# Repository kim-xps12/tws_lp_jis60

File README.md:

# tws_lp_jis60

## About

JIS配列・ロープロファイル・完全無線の左右分割60%キーボードです。

## Concept

[sphh jp v2 (a bit keys)](https://abitkeys.com/sphhjp/build_v2.html) のHHKB-likeなJIS配列を分割化したコンセプトを継承し、完全無線化とロープロファイル化を加えた設計です。

- JIS 60%配列（ISOエンター、矢印キー付き）
- 完全無線（PC接続も左右間もBLE）
- Kailh Choc v2 互換ホットスワップ
- PCBサンドイッチ構造
- ZMK Firmware によるキーマップ変更
- XIAO nRF52840 搭載

設計の詳細は設計者の note 記事を参照してください: [JIS配列でロープロファイルな完全無線の左右分割キーボードを作った話](https://note.com/b_sky_lab/n/n9fbacc2c5264)

## How to Build

ビルドガイドは Web 版（[https://b-sky-lab.github.io/tws_lp_jis60/](https://b-sky-lab.github.io/tws_lp_jis60/)）を参照してください。ソースは [docs/build_guide/build_guide.md](docs/build_guide/build_guide.md) です。

ファームウェア（ZMKシールドモジュール）は [b-sky-lab/tws_lp_shield_module](https://github.com/b-sky-lab/tws_lp_shield_module) で管理されています。

## Where to Get

<!-- TODO: Booth頒布開始後にリンクを追加 -->
準備中

## License

このリポジトリは CC-BY-SA-4.0（Creative Commons Attribution-ShareAlike 4.0 International）でライセンスされています．

詳細は [LICENSE](./LICENSE) を参照してください.

### Third-Party Components

本プロジェクトは，以下の第三者ライブラリのコンポーネントを利用しています：

#### 1. OPL_Kicad_Library (CC-BY-SA-4.0)
- fork元: https://github.com/Seeed-Studio/OPL_Kicad_Library
- fork先: https://github.com/kim-xps12/OPL_Kicad_Library
- ライセンス: CC-BY-SA-4.0
- 変更ファイル: `XIAO-nRF52840-DIP.kicad_mod`（DRCシルク警告の修正）
- 利用箇所: [pcb_data/kicad_library/external/OPL_Kicad_Library](pcb_data/kicad_library/external/OPL_Kicad_Library)（submodule）

#### 2. KiCAD_FootPrint (MIT)
- fork元: https://github.com/Salicylic-acid3/KiCAD_FootPrint
- fork先: https://github.com/kim-xps12/KiCAD_FootPrint
- ライセンス: MIT
- 変更ファイル: `Diode_TH_SMD.kicad_mod`（DRCシルク警告の修正）
- 利用箇所: [pcb_data/kicad_library/external/KiCAD_FootPrint](pcb_data/kicad_library/external/KiCAD_FootPrint)（submodule）

#### 3. MX_V2 (MIT)
- fork元: https://github.com/ai03-2725/MX_V2
- 利用ディレクトリ:[custom-library.pretty](pcb_data/kicad_library/custom-library.pretty)
- ライセンス: MIT
- 派生物: `pcb_data/kicad_library/custom-library.pretty/`内のカスタムフットプリント
- 帰属表示: 当該ディレクトリ内の[LICENSE_MX_V2.txt](pcb_data/kicad_library/custom-library.pretty/LICENSE_MX_V2.txt)を参照

### Why CC-BY-SA-4.0？

本作のライセンスがCC-BY-SA-4.0である理由は，PCB設計ファイルにOPL_Kicad_Libraryから改変したフットプリントを組み込んでいるからです．CC-BY-SA-4.0のShareAlike条項により，派生物も同じCC-BY-SA-4.0ライセンスを継承する必要があります．

MITライセンスのコンポーネント（KiCAD_FootPrint，MX_V2）は，適切な帰属表示を維持することでCC-BY-SA-4.0と互換性があります．

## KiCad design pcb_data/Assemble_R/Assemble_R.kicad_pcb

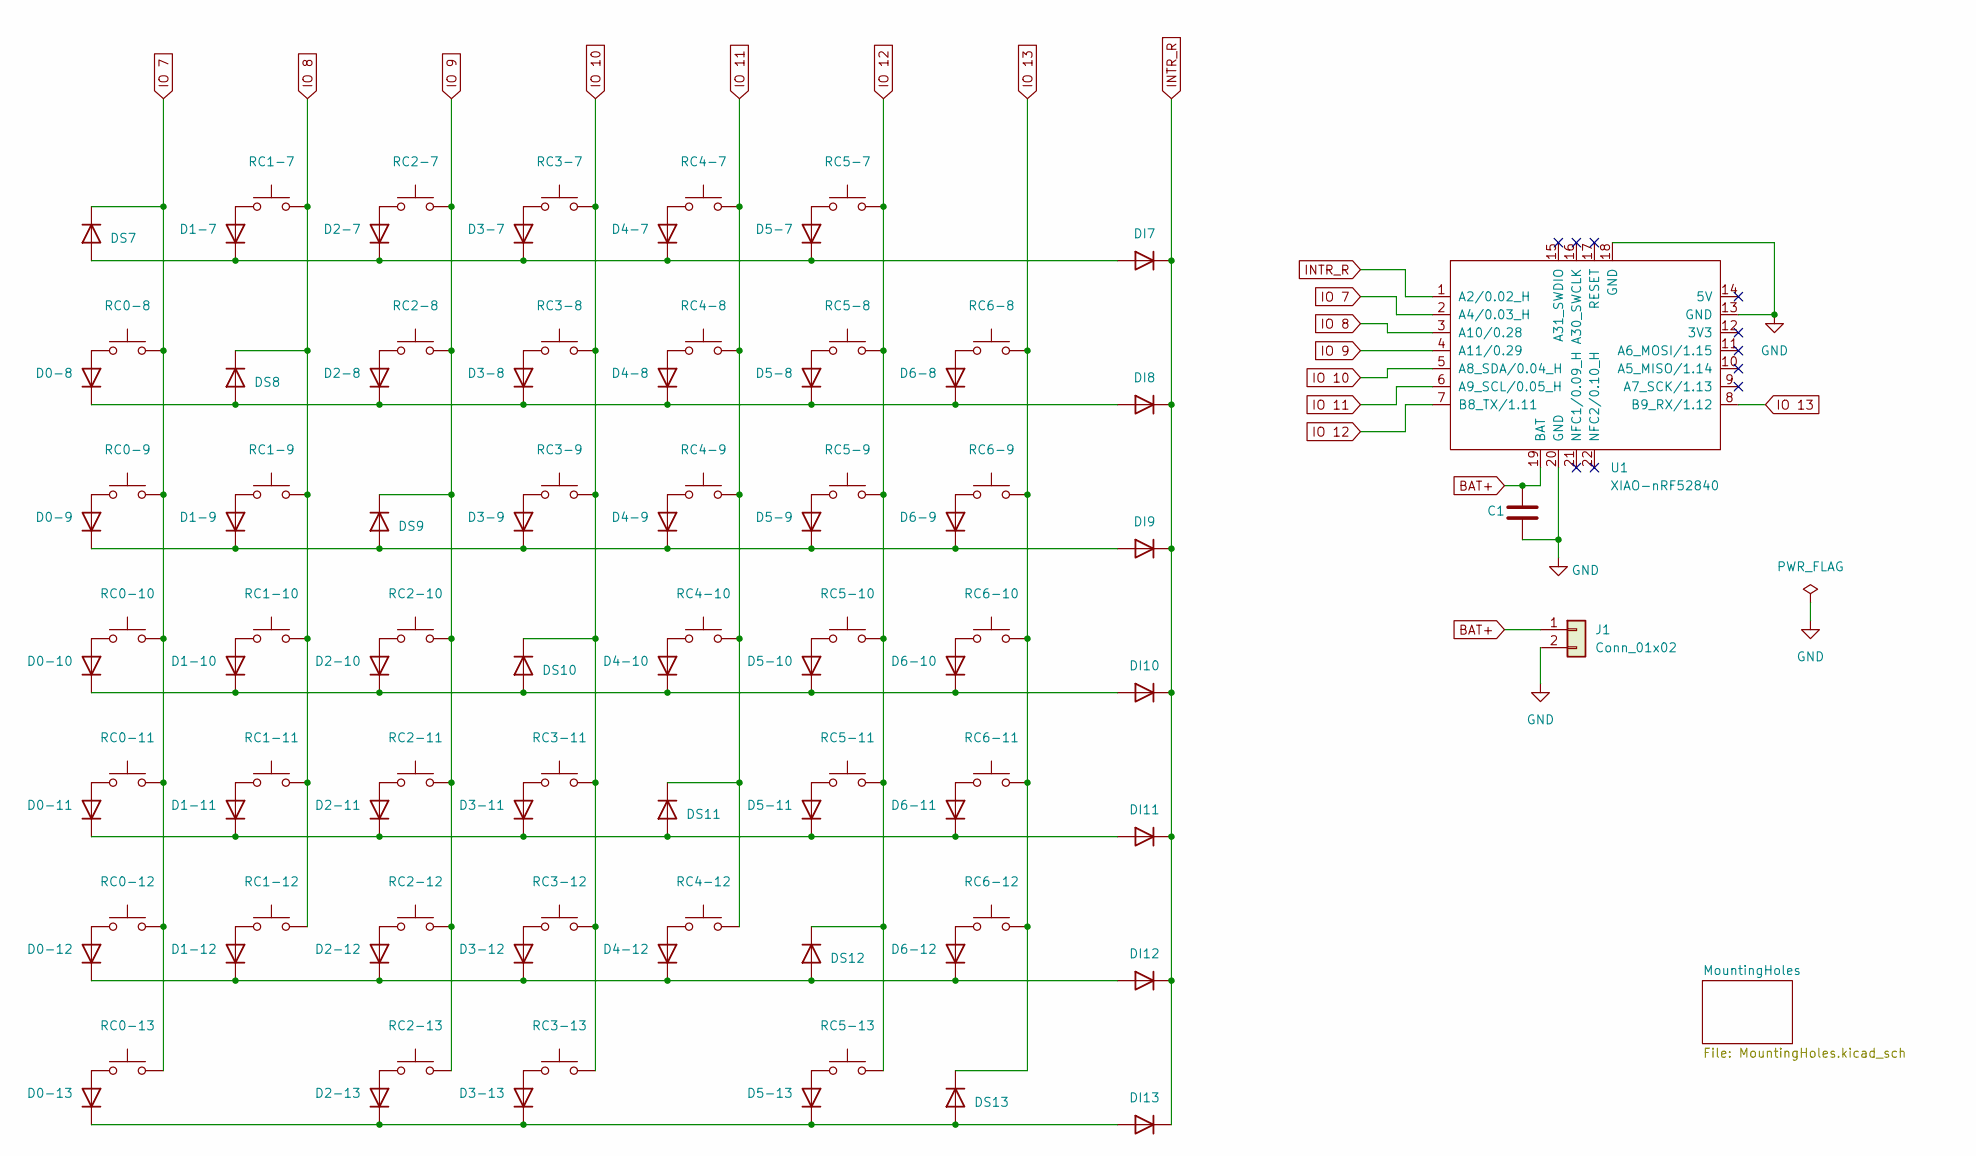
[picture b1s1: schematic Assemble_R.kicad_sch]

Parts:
C1: GRM32EC81C476KE15L; C_1210_3225Metric_Pad1.33x2.70mm_HandSolder
D0-8, D0-9, D0-10, D0-11, D0-12, D0-13, D1-7, D1-9, D1-10, D1-11, D1-12, D2-7, D2-8, D2-10, D2-11, D2-12, D2-13, D3-7, D3-8, D3-9, D3-11, D3-12, D3-13, D4-7, D4-8, D4-9, D4-10, D4-12, D5-7, D5-8, D5-9, D5-10, D5-11, D5-13, D6-8, D6-9, D6-10, D6-11, D6-12: 1N4148W; Diode_TH_SMD
DI7, DI8, DI9, DI10, DI11, DI12, DI13: 1N4148W; Diode_TH_SMD
DS7, DS8, DS9, DS10, DS11, DS12, DS13: 1N4148W; Diode_TH_SMD
J1: Conn_01x02; JST_PH_B2B-PH-K_1x02_P2.00mm_Vertical
RC0-8, RC0-9, RC0-10, RC0-11, RC0-12, RC1-7, RC1-9, RC1-10, RC1-11, RC1-12, RC2-7, RC2-8, RC2-10, RC2-11, RC2-12, RC2-13, RC3-7, RC3-8, RC3-9, RC3-11, RC3-12, RC3-13, RC4-7, RC4-8, RC4-9, RC4-10, RC4-12, RC5-7, RC5-8, RC5-9, RC5-10, RC5-11, RC5-13, RC6-8, RC6-9, RC6-11, RC6-12: SW_Push; Kailh-PG1353-Hotswap-R-1U
RC0-13: SW_Push; Kailh-PG1353-Hotswap-R-1.25U
RC6-10: SW_Push; Kailh-PG1353-Hotswap-ISOEnter-R
U1: XIAO-nRF52840; xiao-ble-smd-cutout

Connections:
BAT+: C1.1, J1.1, U1.19 (BAT)
GND: C1.2, J1.2, U1.13 (GND), U1.18 (GND), U1.20 (GND)
INTR_R: DI7.1 (K), DI8.1 (K), DI9.1 (K), DI10.1 (K), DI11.1 (K), DI12.1 (K), DI13.1 (K), U1.1 (A2/0.02_H)
IO 7: DS7.1 (K), RC0-8.1, RC0-9.1, RC0-10.1, RC0-11.1, RC0-12.1, RC0-13.1, U1.2 (A4/0.03_H)
IO 8: DS8.1 (K), RC1-7.1, RC1-9.1, RC1-10.1, RC1-11.1, RC1-12.1, U1.3 (A10/0.28)
IO 9: DS9.1 (K), RC2-7.1, RC2-8.1, RC2-10.1, RC2-11.1, RC2-12.1, RC2-13.1, U1.4 (A11/0.29)
IO 10: DS10.1 (K), RC3-7.1, RC3-8.1, RC3-9.1, RC3-11.1, RC3-12.1, RC3-13.1, U1.5 (A8_SDA/0.04_H)
IO 11: DS11.1 (K), RC4-7.1, RC4-8.1, RC4-9.1, RC4-10.1, RC4-12.1, U1.6 (A9_SCL/0.05_H)
IO 12: DS12.1 (K), RC5-7.1, RC5-8.1, RC5-9.1, RC5-10.1, RC5-11.1, RC5-13.1, U1.7 (B8_TX/1.11)
IO 13: DS13.1 (K), RC6-8.1, RC6-9.1, RC6-10.1, RC6-11.1, RC6-12.1, U1.8 (B9_RX/1.12)
unnamed: D0-8.2 (A), RC0-8.2
unnamed: D0-8.1 (K), D2-8.1 (K), D3-8.1 (K), D4-8.1 (K), D5-8.1 (K), D6-8.1 (K), DI8.2 (A), DS8.2 (A)
unnamed: D0-9.2 (A), RC0-9.2
unnamed: D0-9.1 (K), D1-9.1 (K), D3-9.1 (K), D4-9.1 (K), D5-9.1 (K), D6-9.1 (K), DI9.2 (A), DS9.2 (A)
unnamed: D0-10.2 (A), RC0-10.2
unnamed: D0-10.1 (K), D1-10.1 (K), D2-10.1 (K), D4-10.1 (K), D5-10.1 (K), D6-10.1 (K), DI10.2 (A), DS10.2 (A)
unnamed: D0-11.2 (A), RC0-11.2
unnamed: D0-11.1 (K), D1-11.1 (K), D2-11.1 (K), D3-11.1 (K), D5-11.1 (K), D6-11.1 (K), DI11.2 (A), DS11.2 (A)
unnamed: D0-12.2 (A), RC0-12.2
unnamed: D0-12.1 (K), D1-12.1 (K), D2-12.1 (K), D3-12.1 (K), D4-12.1 (K), D6-12.1 (K), DI12.2 (A), DS12.2 (A)
unnamed: D0-13.2 (A), RC0-13.2
unnamed: D0-13.1 (K), D2-13.1 (K), D3-13.1 (K), D5-13.1 (K), DI13.2 (A), DS13.2 (A)
unnamed: D1-7.2 (A), RC1-7.2
unnamed: D1-7.1 (K), D2-7.1 (K), D3-7.1 (K), D4-7.1 (K), D5-7.1 (K), DI7.2 (A), DS7.2 (A)
unnamed: D1-9.2 (A), RC1-9.2
unnamed: D1-10.2 (A), RC1-10.2
unnamed: D1-11.2 (A), RC1-11.2
unnamed: D1-12.2 (A), RC1-12.2
unnamed: D2-7.2 (A), RC2-7.2
unnamed: D2-8.2 (A), RC2-8.2
unnamed: D2-10.2 (A), RC2-10.2
unnamed: D2-11.2 (A), RC2-11.2
unnamed: D2-12.2 (A), RC2-12.2
unnamed: D2-13.2 (A), RC2-13.2
unnamed: D3-7.2 (A), RC3-7.2
unnamed: D3-8.2 (A), RC3-8.2
unnamed: D3-9.2 (A), RC3-9.2
unnamed: D3-11.2 (A), RC3-11.2
unnamed: D3-12.2 (A), RC3-12.2
unnamed: D3-13.2 (A), RC3-13.2
unnamed: D4-7.2 (A), RC4-7.2
unnamed: D4-8.2 (A), RC4-8.2
unnamed: D4-9.2 (A), RC4-9.2
unnamed: D4-10.2 (A), RC4-10.2
unnamed: D4-12.2 (A), RC4-12.2
unnamed: D5-7.2 (A), RC5-7.2
unnamed: D5-8.2 (A), RC5-8.2
unnamed: D5-9.2 (A), RC5-9.2
unnamed: D5-10.2 (A), RC5-10.2
unnamed: D5-11.2 (A), RC5-11.2
unnamed: D5-13.2 (A), RC5-13.2
unnamed: D6-8.2 (A), RC6-8.2
unnamed: D6-9.2 (A), RC6-9.2
unnamed: D6-10.2 (A), RC6-10.2
unnamed: D6-11.2 (A), RC6-11.2
unnamed: D6-12.2 (A), RC6-12.2

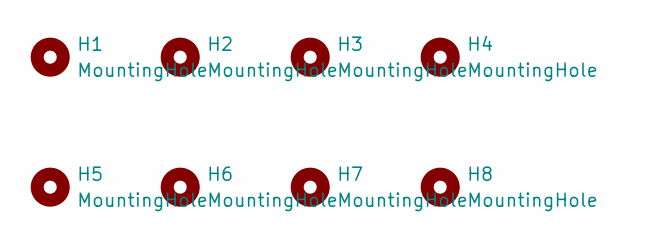
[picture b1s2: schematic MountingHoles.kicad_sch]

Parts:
H1, H2, H3, H4, H5, H6, H7, H8: MountingHole; m2_Spacer_Hole

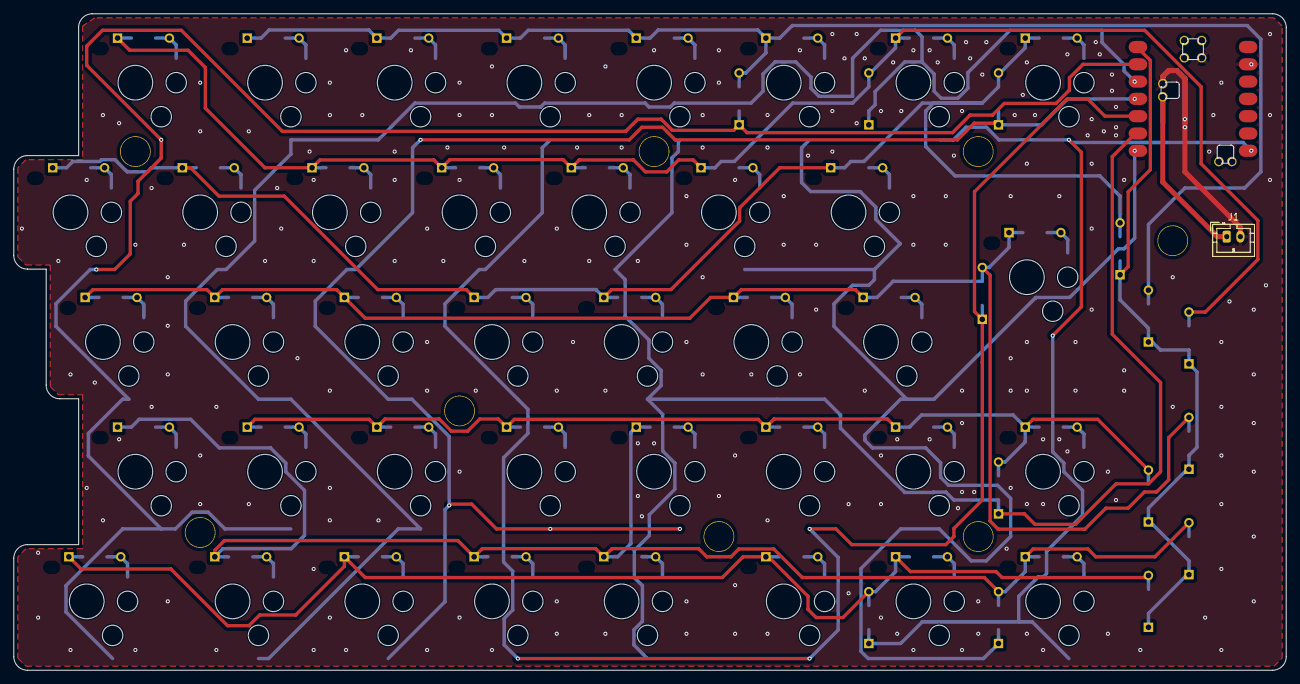
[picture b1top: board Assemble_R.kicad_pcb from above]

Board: 2 copper layers, 186.9 x 96.4 mm, 103 parts (1 on the bottom side), 56 nets.

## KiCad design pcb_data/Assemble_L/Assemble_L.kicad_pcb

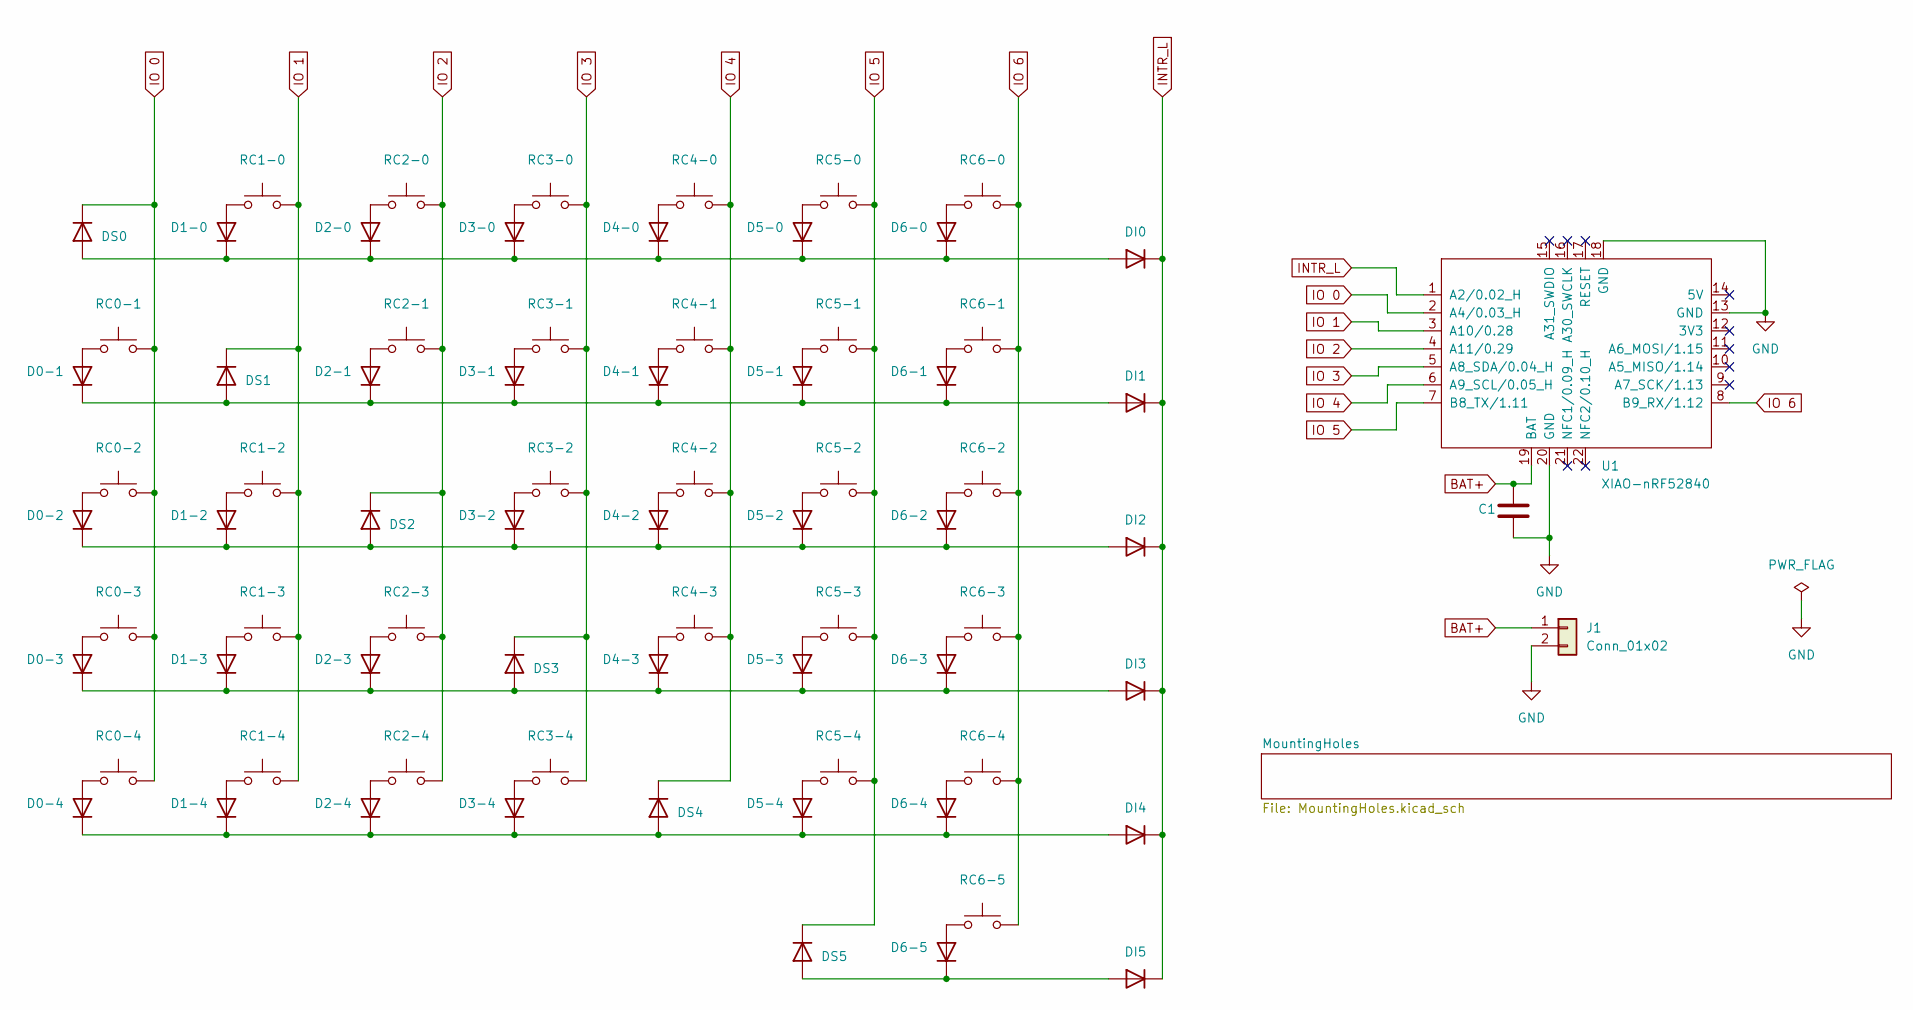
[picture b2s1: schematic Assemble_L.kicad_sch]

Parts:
C1: GRM32EC81C476KE15L; C_1210_3225Metric_Pad1.33x2.70mm_HandSolder
D0-1, D0-2, D0-3, D0-4, D1-0, D1-2, D1-3, D1-4, D2-0, D2-1, D2-3, D2-4, D3-0, D3-1, D3-2, D3-4, D4-0, D4-1, D4-2, D4-3, D5-0, D5-1, D5-2, D5-3, D5-4, D6-0, D6-1, D6-2, D6-3, D6-4, D6-5: 1N4148W; Diode_TH_SMD
DI0, DI1, DI2, DI3, DI4, DI5: 1N4148W; Diode_TH_SMD
DS0, DS1, DS2, DS3, DS4, DS5: 1N4148W; Diode_TH_SMD
J1: Conn_01x02; JST_PH_B2B-PH-K_1x02_P2.00mm_Vertical
RC0-1: SW_Push; Kailh-PG1353-Hotswap-L-1.5U
RC0-2: SW_Push; Kailh-PG1353-Hotswap-L-1.75U
RC0-3: SW_Push; Kailh-PG1353-Hotswap-L-2U
RC0-4, RC1-0, RC1-2, RC1-3, RC1-4, RC2-0, RC2-1, RC2-3, RC2-4, RC3-0, RC3-1, RC3-2, RC3-4, RC4-0, RC4-1, RC4-2, RC4-3, RC5-0, RC5-1, RC5-2, RC5-3, RC5-4, RC6-0, RC6-1, RC6-2, RC6-3, RC6-4: SW_Push; Kailh-PG1353-Hotswap-L-1U
RC6-5: SW_Push; Kailh-PG1353-Hotswap-L-1.25U
U1: XIAO-nRF52840; xiao-ble-smd-cutout

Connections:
BAT+: C1.1, J1.1, U1.19 (BAT)
GND: C1.2, J1.2, U1.13 (GND), U1.18 (GND), U1.20 (GND)
INTR_L: DI0.1 (K), DI1.1 (K), DI2.1 (K), DI3.1 (K), DI4.1 (K), DI5.1 (K), U1.1 (A2/0.02_H)
IO 0: DS0.1 (K), RC0-1.1, RC0-2.1, RC0-3.1, RC0-4.1, U1.2 (A4/0.03_H)
IO 1: DS1.1 (K), RC1-0.1, RC1-2.1, RC1-3.1, RC1-4.1, U1.3 (A10/0.28)
IO 2: DS2.1 (K), RC2-0.1, RC2-1.1, RC2-3.1, RC2-4.1, U1.4 (A11/0.29)
IO 3: DS3.1 (K), RC3-0.1, RC3-1.1, RC3-2.1, RC3-4.1, U1.5 (A8_SDA/0.04_H)
IO 4: DS4.1 (K), RC4-0.1, RC4-1.1, RC4-2.1, RC4-3.1, U1.6 (A9_SCL/0.05_H)
IO 5: DS5.1 (K), RC5-0.1, RC5-1.1, RC5-2.1, RC5-3.1, RC5-4.1, U1.7 (B8_TX/1.11)
IO 6: RC6-0.1, RC6-1.1, RC6-2.1, RC6-3.1, RC6-4.1, RC6-5.1, U1.8 (B9_RX/1.12)
unnamed: D0-1.2 (A), RC0-1.2
unnamed: D0-1.1 (K), D2-1.1 (K), D3-1.1 (K), D4-1.1 (K), D5-1.1 (K), D6-1.1 (K), DI1.2 (A), DS1.2 (A)
unnamed: D0-2.2 (A), RC0-2.2
unnamed: D0-2.1 (K), D1-2.1 (K), D3-2.1 (K), D4-2.1 (K), D5-2.1 (K), D6-2.1 (K), DI2.2 (A), DS2.2 (A)
unnamed: D0-3.2 (A), RC0-3.2
unnamed: D0-3.1 (K), D1-3.1 (K), D2-3.1 (K), D4-3.1 (K), D5-3.1 (K), D6-3.1 (K), DI3.2 (A), DS3.2 (A)
unnamed: D0-4.2 (A), RC0-4.2
unnamed: D0-4.1 (K), D1-4.1 (K), D2-4.1 (K), D3-4.1 (K), D5-4.1 (K), D6-4.1 (K), DI4.2 (A), DS4.2 (A)
unnamed: D1-0.2 (A), RC1-0.2
unnamed: D1-0.1 (K), D2-0.1 (K), D3-0.1 (K), D4-0.1 (K), D5-0.1 (K), D6-0.1 (K), DI0.2 (A), DS0.2 (A)
unnamed: D1-2.2 (A), RC1-2.2
unnamed: D1-3.2 (A), RC1-3.2
unnamed: D1-4.2 (A), RC1-4.2
unnamed: D2-0.2 (A), RC2-0.2
unnamed: D2-1.2 (A), RC2-1.2
unnamed: D2-3.2 (A), RC2-3.2
unnamed: D2-4.2 (A), RC2-4.2
unnamed: D3-0.2 (A), RC3-0.2
unnamed: D3-1.2 (A), RC3-1.2
unnamed: D3-2.2 (A), RC3-2.2
unnamed: D3-4.2 (A), RC3-4.2
unnamed: D4-0.2 (A), RC4-0.2
unnamed: D4-1.2 (A), RC4-1.2
unnamed: D4-2.2 (A), RC4-2.2
unnamed: D4-3.2 (A), RC4-3.2
unnamed: D5-0.2 (A), RC5-0.2
unnamed: D5-1.2 (A), RC5-1.2
unnamed: D5-2.2 (A), RC5-2.2
unnamed: D5-3.2 (A), RC5-3.2
unnamed: D5-4.2 (A), RC5-4.2
unnamed: D6-0.2 (A), RC6-0.2
unnamed: D6-1.2 (A), RC6-1.2
unnamed: D6-2.2 (A), RC6-2.2
unnamed: D6-3.2 (A), RC6-3.2
unnamed: D6-4.2 (A), RC6-4.2
unnamed: D6-5.2 (A), RC6-5.2
unnamed: D6-5.1 (K), DI5.2 (A), DS5.2 (A)

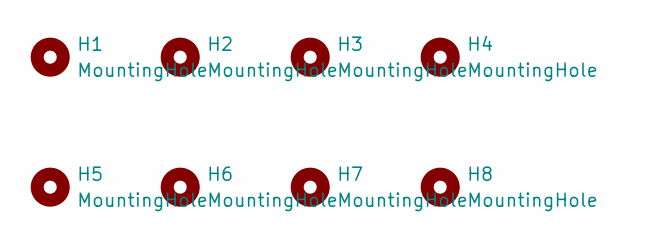
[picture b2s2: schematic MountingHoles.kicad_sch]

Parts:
H1, H2, H3, H4, H5, H6, H7, H8: MountingHole; m2_Spacer_Hole

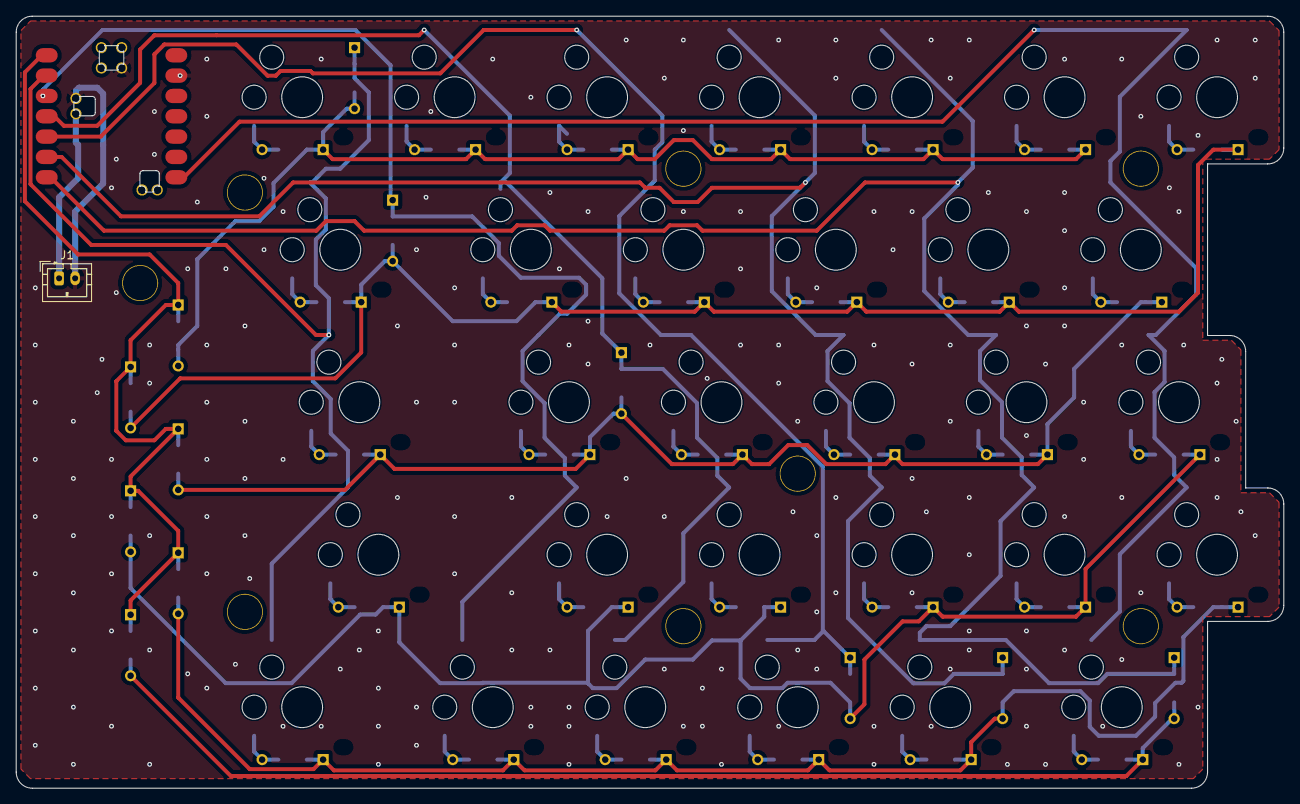
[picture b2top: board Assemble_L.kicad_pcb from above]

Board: 2 copper layers, 158.4 x 96.4 mm, 85 parts (1 on the bottom side), 47 nets.

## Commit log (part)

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2025-12-03 add .gitignore
2025-12-03 Add submodule: OPL_Kicad_Library
2025-12-03 Add submodule: MX_V2
2025-12-03 Add submodule: KiCAD_FootPrint
2025-12-03 add keyboard layout file
2025-12-03 add custom fp
2025-12-03 add kicad file
2025-12-06 complete to design pattern of board L
2025-12-06 Update submodules: resolve DRC warning about silk
2025-12-06 Update submodule URLs to kim-xps12 forks
2025-12-07 fix line width 0.2 -> 0.5
2025-12-07 add GND plane
2025-12-07 complete to design pattern of board R
2025-12-07 add README and LICENCE of custom footprint
2025-12-07 update foot print reference, and fix GND filling area DRC error
2025-12-07 add 3d model
2025-12-07 add licence details
2025-12-17 add licence details (#3)
    マージして閉じます
2025-12-17 Feat/add kicad pro (#4)
    * add .gitignore
    * Add submodule: OPL_Kicad_Library
    * Add submodule: MX_V2
    * Add submodule: KiCAD_FootPrint
    * update .gitignore
    * add keyboard layout file
2025-12-17 add mount hole
2025-12-17 add plugin for jlcpcb
2025-12-17 add production.zip
2025-12-17 add mount hole (#5)
    ネジ穴を追加しました．
    特にレビュー項目はない（git logを綺麗に残すためのPR）のでセルフマージします．
2025-12-17 Feat/add plugin for jlcpcb (#6)
    * add mount hole
    * add plugin for jlcpcb
    * add production.zip
2025-12-30 update .gitignore (#7)
2025-12-30 update fp table
2025-12-30 copy from assemble
2025-12-30 remove zone
2025-12-30 remove segment
2025-12-30 remove via
2025-12-30 remove diode
2025-12-30 replace fp
2025-12-30 replace fp (m2 screw hole)
2025-12-30 add step file
2025-12-30 add xiao-ble library for cut hole
2025-12-30 replace footprint of xiao-nrf52840
2025-12-30 change remote url, ssh --> https
2025-12-30 Update KiCAD_FootPrint submodule to kim-xps12 fork
2025-12-30 Update OPL_Kicad_Library submodule to kim-xps12 fork
2025-12-30 add GND beta
2025-12-30 replace symbol of xiao-ble
2026-01-03 import library
2026-01-03 remove library
2026-01-03 Issue/11 update xiao ble symbol and footprint (#18)
2026-01-03 add component-class field
2026-01-03 add custom design rule
2026-01-03 apply footprint update, and fix patterns
2026-01-03 Issue/19 apply castellated hole setting (#20)
    * add component-class field
    * add custom design rule
    * apply footprint update, and fix patterns
2026-01-03 add kbd_hole lib
2026-01-03 add mount hole component
2026-01-03 add mount hole, and fix patterns
2026-01-03 project file updated
2026-01-03 add mounting holes schematics
2026-01-03 step files updates
2026-01-04 add Capacitor symbol
2026-01-04 add Capacitor foot print
2026-01-04 add model number of capacitor
2026-01-04 Issue/21 add capacitor bat gnd (#23)
    * add Capacitor symbol
    * add Capacitor foot print
    * project file updated
    * add model number of capacitor
2026-01-04 tune hole positions
2026-01-04 fix power line pattern width
2026-01-05 Feat/fix power line width (#24)
    * fix power line pattern width
    * project file updated
2026-01-05 tune hole position near by xiao
2026-01-05 step files updated
2026-01-06 Issue/14 change hole position (#22)
    * add kbd_hole lib
    * add mount hole component
    * add mount hole, and fix patterns
    * project file updated
    * add mounting holes schematics
    * step files updates
2026-01-08 remove file
2026-01-08 rename file
2026-01-08 replace value
2026-01-08 fix position of mounting hole
2026-01-08 copy from Assemble_L
2026-01-09 remove segment and via
2026-01-09 replace switch footprint
2026-01-09 update line
2026-01-09 update footprint
2026-01-09 remove unnecessary footprint
2026-01-09 change hole position
2026-01-09 step updated
2026-01-09 add bottom_l project file
2026-01-10 copy from Assemble_R
2026-01-10 remove zone, segment and via
2026-01-10 add bottom_r project file
2026-01-10 fix hole footprint and number
2026-01-10 fix hole footprint and number (#25)
2026-01-11 fix line
2026-05-26 add build guide
2026-05-27 update build guide
2026-06-05 Issue/12 build guide (#28)
    * add build guide
    * update build guide
    * Update docs/requirements/requirements_board.md
    * Update docs/requirements/requirements_board.md
    * Update docs/requirements/requirements_board.md
    * Update docs/requirements/requirements_board.md
2026-06-05 Issue/15 top and bottom plate (#26)
    * copy from Assemble
    * remove file
    * rename file
    * remove file
    * replace value
    * fix position of mounting hole
2026-06-05 ビルドガイドのディレクトリ整理
2026-06-05 不要なプレースホルダーを削除
2026-06-05 キット内容と別途購入品リストを更新
2026-06-05 工具購入先とAmazonアフィリンクの但し書きを追加
2026-06-05 キット内容の画像を追加
2026-06-05 基板の左右裏表のラベリングを追加
2026-06-05 ハンダ付けのセクションを更新
2026-06-05 組み立てのセクションを刷新
2026-06-05 ファームウェアのセクションを更新
2026-06-05 トラブルシュートのセクションを更新
2026-06-05 参考リンクなどを整理
2026-06-05 バッテリーカバー，ゴム足，組み立て完成のセクションを追加
2026-06-05 ファーム書き込み手順を追記
2026-06-05 句読点をカンマドットに統一
2026-06-05 完成品画像に注釈を追加
2026-06-05 xiao背面半田付けの参考画像を追加
2026-06-05 キー配置ミスの画像を差し替え
2026-06-05 Issue/12 build guide (#29)
    * ビルドガイドのディレクトリ整理
    * 不要なプレースホルダーを削除
    * キット内容と別途購入品リストを更新
    * 工具購入先とAmazonアフィリンクの但し書きを追加
    * キット内容の画像を追加
    * 基板の左右裏表のラベリングを追加
2026-06-05 ファームウェアのリポジトリURLを修正
2026-06-05 完成品の写真をREADMEにも追加
2026-06-05 Feat/update readme (#34)
    * ファームウェアのリポジトリURLを修正
    * 完成品の写真をREADMEにも追加
2026-06-05 完成写真をビルドガイドのトップへ移動
2026-06-05 完成写真をビルドガイドのトップへ移動 (#37)
2026-06-05 バッテリーカバーの注釈を追記
